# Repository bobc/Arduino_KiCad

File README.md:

# Arduino projects converted to KiCad

This repository contains Eagle projects that have been automatically converted to KiCad (v4) format  by eakit.

The conversion is as far as possible identical to the original, but some features of Eagle cannot be converted directly to KiCad. 

They may (probably will) contain conversion errors - use at own risk!

If you find a conversion problem, please raise an issue here. In case of doubt, the Eagle project should be preferred. 

If you find a problem with the design of a project, or wish to make a feature request,
please do not raise an issue here, contact the original designers.

## Copyright

Copyrights and license terms for each project are as specified by original author(s). 

## Trademarks

Please respect trademarks where applicable, and do not use without permission. 

- "Arduino", "Genuino", and the Arduino logo are trademarks of Arduino AG. https://www.arduino.cc/en/Main/CopyrightNotice

## eakit

eakit project: https://github.com/bobc/eakit

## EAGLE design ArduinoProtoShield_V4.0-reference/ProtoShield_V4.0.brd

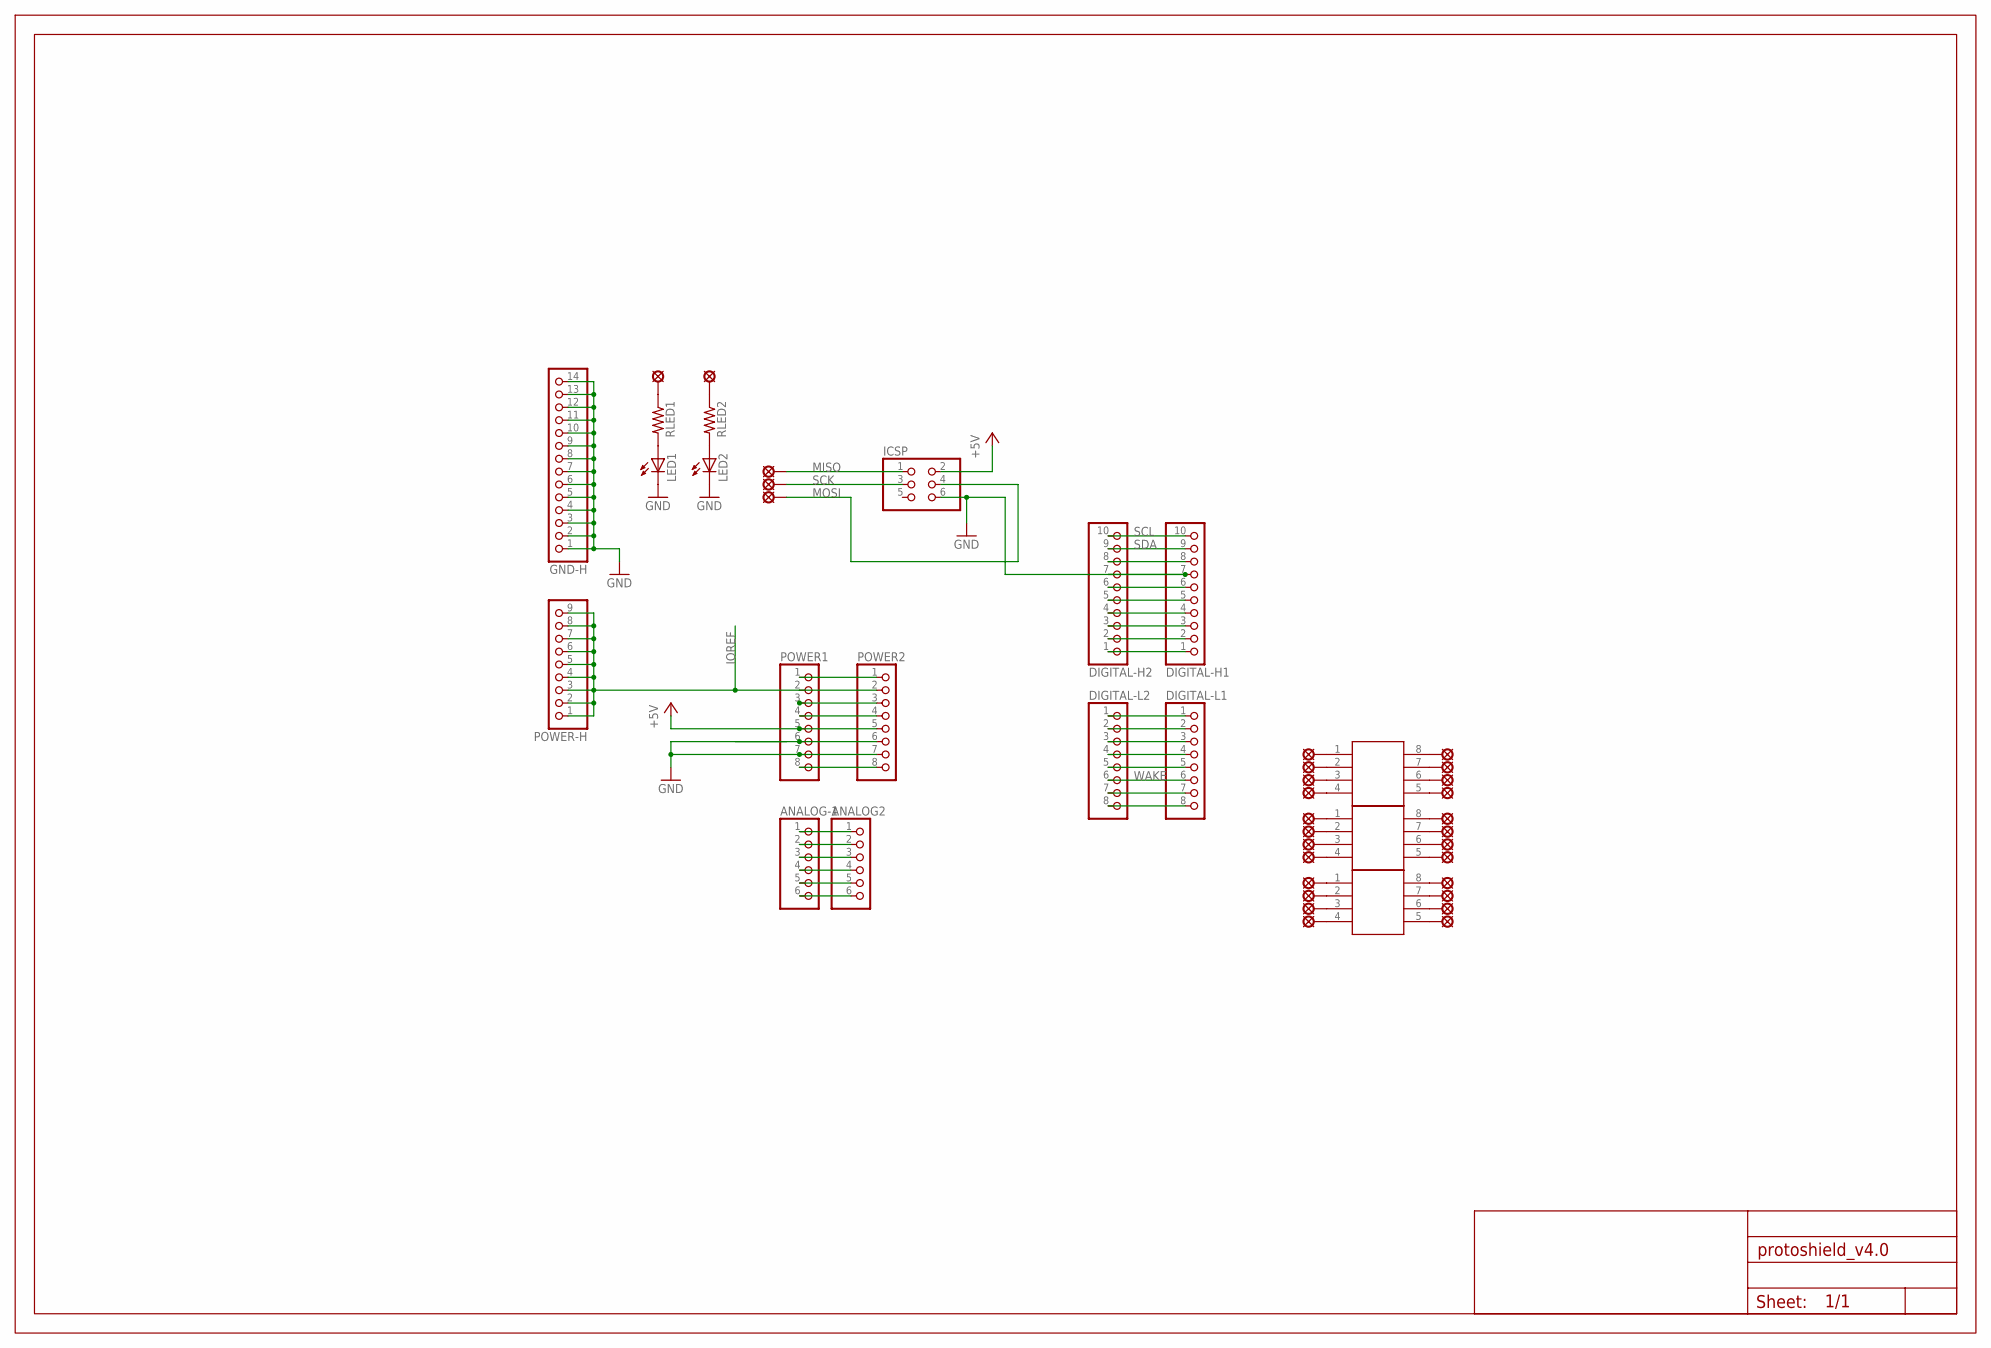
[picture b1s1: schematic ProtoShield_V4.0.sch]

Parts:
ANALOG2: PINHD-1X6; 1X06
ANALOG-1: PINHD-1X6; 1X06
DIGITAL-H1, DIGITAL-H2: PINHD-1X10TH; 1X10-TH
DIGITAL-L1, DIGITAL-L2: PINHD-1X8; 1X08; MPN B67345B0001X087
FRAME1: A3L-LOC; FRAME
GND-H: PINHD-1X14; 1X14; MPN 08051C472KAZ2A
IC1, IC2, IC3: SMD-8; SO-8; MPN MAL215374221E3
ICSP: PINHD-2X3; 2X03; MPN SSF22X035
LED1, LED2: LED3MM; MPN 553-0711F
MISO: LSP10; MPN MDLSP1-04M-01
MOSI: LSP10; MPN MDLSP1-04M-01
P1, P2, P3, P4, P5, P6, P7, P8, P9, P10, P11, P12, P13, P14, P15, P16, P17, P18, P19, P20, P21, P22, P23, P24: LSP10; MPN MDLSP1-04M-01
PLED1, PLED2: LSP10; MPN MDLSP1-04M-01
POWER1, POWER2: PINHD-1X8TH; 1X08-TH
POWER-H: PINHD-1X9; 1X9; MPN 513LF
RLED1, RLED2: 6MM.3; R0207/3
SCK: LSP10; MPN MDLSP1-04M-01

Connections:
+5V: ICSP.2, POWER1.5, POWER2.5
GND: DIGITAL-H1.7, DIGITAL-H2.7, GND-H.1, GND-H.2, GND-H.3, GND-H.4, GND-H.5, GND-H.6, GND-H.7, GND-H.8, GND-H.9, GND-H.10, GND-H.11, GND-H.12, GND-H.13, GND-H.14, ICSP.6, LED1.K (C), LED2.K (C), POWER1.7, POWER2.7
IOREF: POWER1.2, POWER2.2, POWER-H.1, POWER-H.2, POWER-H.3, POWER-H.4, POWER-H.5, POWER-H.6, POWER-H.7, POWER-H.8, POWER-H.9
MISO: ICSP.1, MISO.MP
MOSI: ICSP.4, MOSI.MP
unnamed: DIGITAL-H1.6, DIGITAL-H2.6
unnamed: DIGITAL-H1.1, DIGITAL-H2.1
unnamed: DIGITAL-H1.4, DIGITAL-H2.4
unnamed: DIGITAL-H1.5, DIGITAL-H2.5
unnamed: IC1.1, P1.MP
unnamed: DIGITAL-H1.2, DIGITAL-H2.2
unnamed: DIGITAL-H1.3, DIGITAL-H2.3
unnamed: DIGITAL-L1.1, DIGITAL-L2.1
unnamed: DIGITAL-L1.2, DIGITAL-L2.2
unnamed: DIGITAL-L1.3, DIGITAL-L2.3
unnamed: DIGITAL-L1.4, DIGITAL-L2.4
unnamed: DIGITAL-L1.5, DIGITAL-L2.5
unnamed: DIGITAL-L1.7, DIGITAL-L2.7
unnamed: DIGITAL-L1.8, DIGITAL-L2.8
unnamed: ANALOG2.1, ANALOG-1.1
unnamed: ANALOG2.2, ANALOG-1.2
unnamed: ANALOG2.3, ANALOG-1.3
unnamed: ANALOG2.4, ANALOG-1.4
unnamed: ANALOG2.5, ANALOG-1.5
unnamed: ANALOG2.6, ANALOG-1.6
unnamed: IC1.2, P2.MP
unnamed: POWER1.6, POWER2.6
unnamed: POWER1.3, POWER2.3
unnamed: POWER1.8, POWER2.8
unnamed: POWER1.1, POWER2.1
unnamed: IC1.3, P3.MP
unnamed: IC1.4, P4.MP
unnamed: IC1.8, P24.MP
unnamed: IC1.7, P23.MP
unnamed: IC1.6, P22.MP
unnamed: IC1.5, P21.MP
unnamed: IC2.1, P5.MP
unnamed: IC2.2, P6.MP
unnamed: IC2.3, P7.MP
unnamed: IC2.4, P8.MP
unnamed: IC2.8, P20.MP
unnamed: IC2.7, P19.MP
unnamed: IC2.6, P18.MP
unnamed: IC2.5, P17.MP
unnamed: IC3.1, P9.MP
unnamed: IC3.2, P10.MP
unnamed: IC3.3, P11.MP
unnamed: IC3.4, P12.MP
unnamed: IC3.8, P16.MP
unnamed: IC3.7, P15.MP
unnamed: IC3.6, P14.MP
unnamed: IC3.5, P13.MP
unnamed: LED2.A, RLED2.2
unnamed: LED1.A, RLED1.2
unnamed: PLED1.MP, RLED1.1
unnamed: PLED2.MP, RLED2.1
unnamed: DIGITAL-H1.8, DIGITAL-H2.8
unnamed: POWER1.4, POWER2.4
SCK: ICSP.3, SCK.MP
SCL: DIGITAL-H1.10, DIGITAL-H2.10
SDA: DIGITAL-H1.9, DIGITAL-H2.9
WAKE: DIGITAL-L1.6, DIGITAL-L2.6

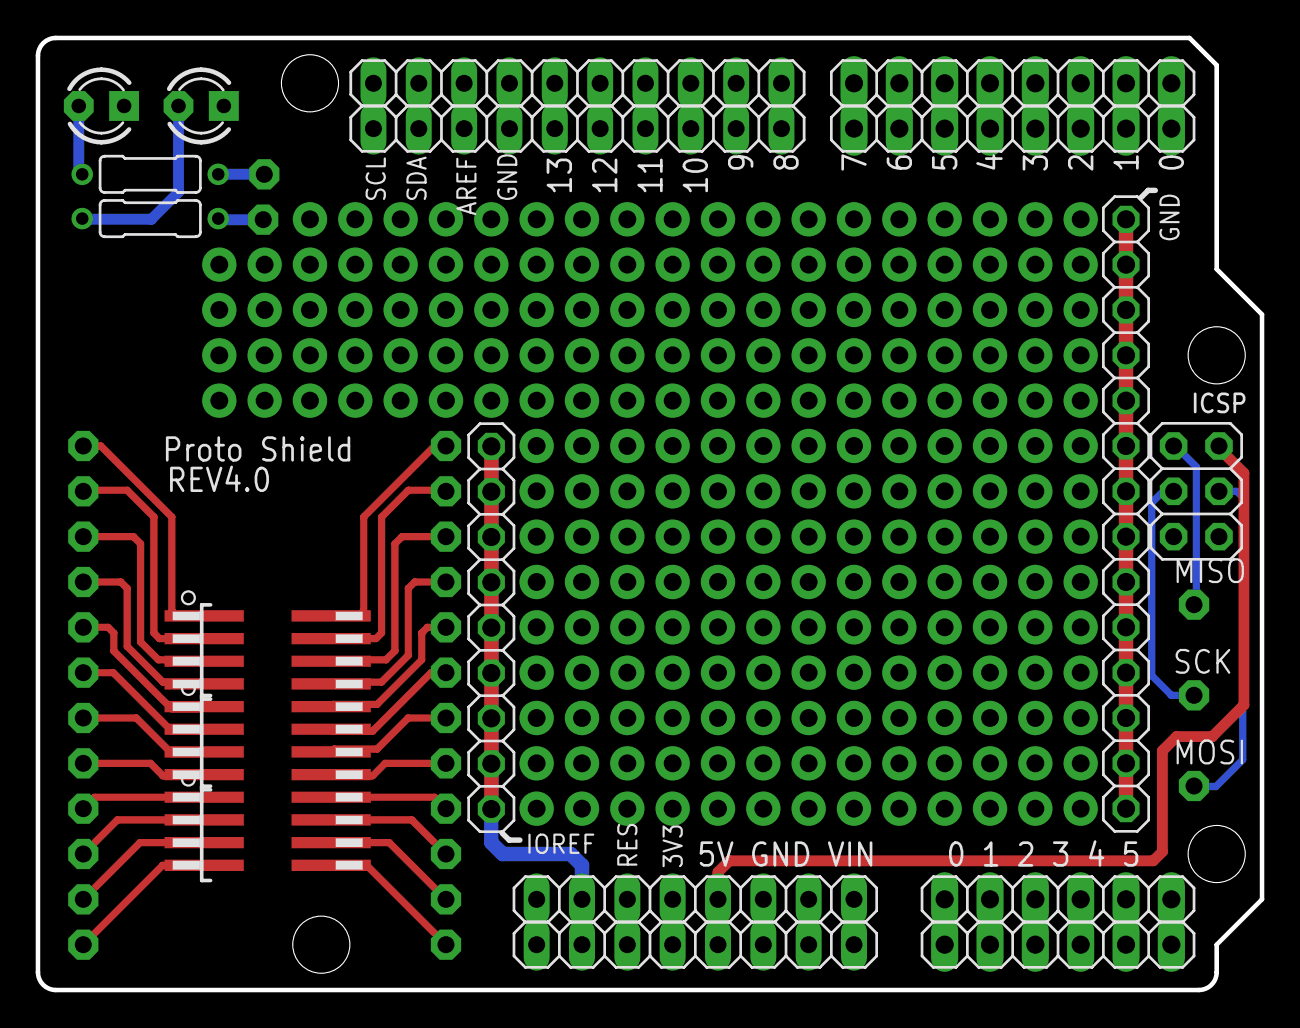
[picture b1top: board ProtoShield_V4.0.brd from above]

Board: 2 copper layers, 68.6 x 53.3 mm, 48 parts (0 on the bottom side), 62 nets.

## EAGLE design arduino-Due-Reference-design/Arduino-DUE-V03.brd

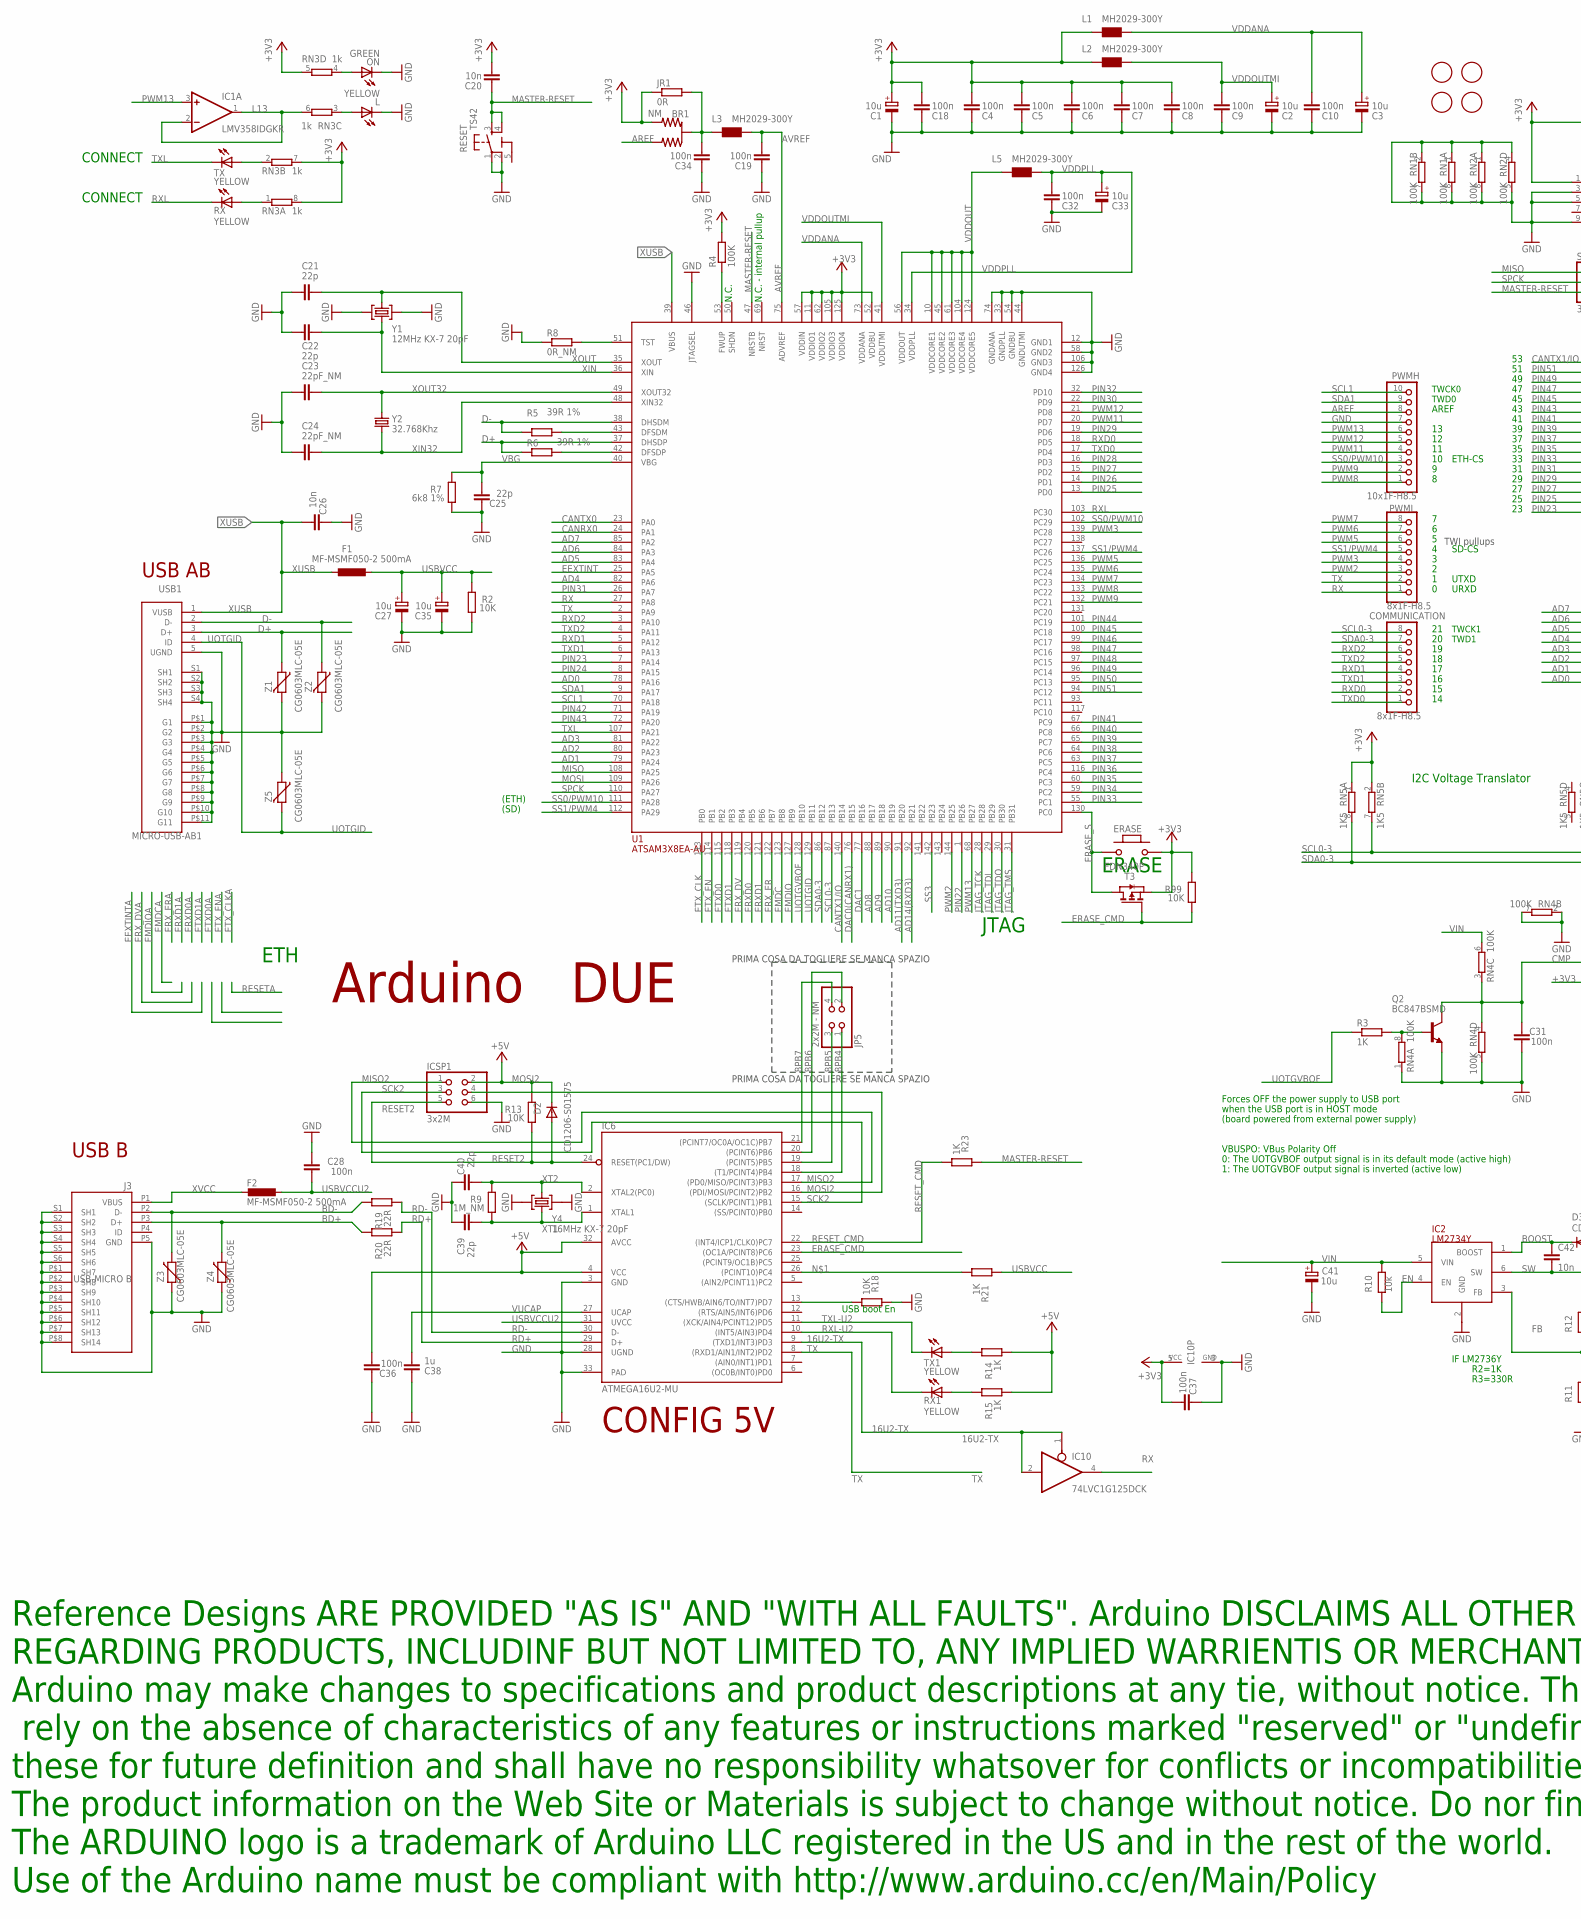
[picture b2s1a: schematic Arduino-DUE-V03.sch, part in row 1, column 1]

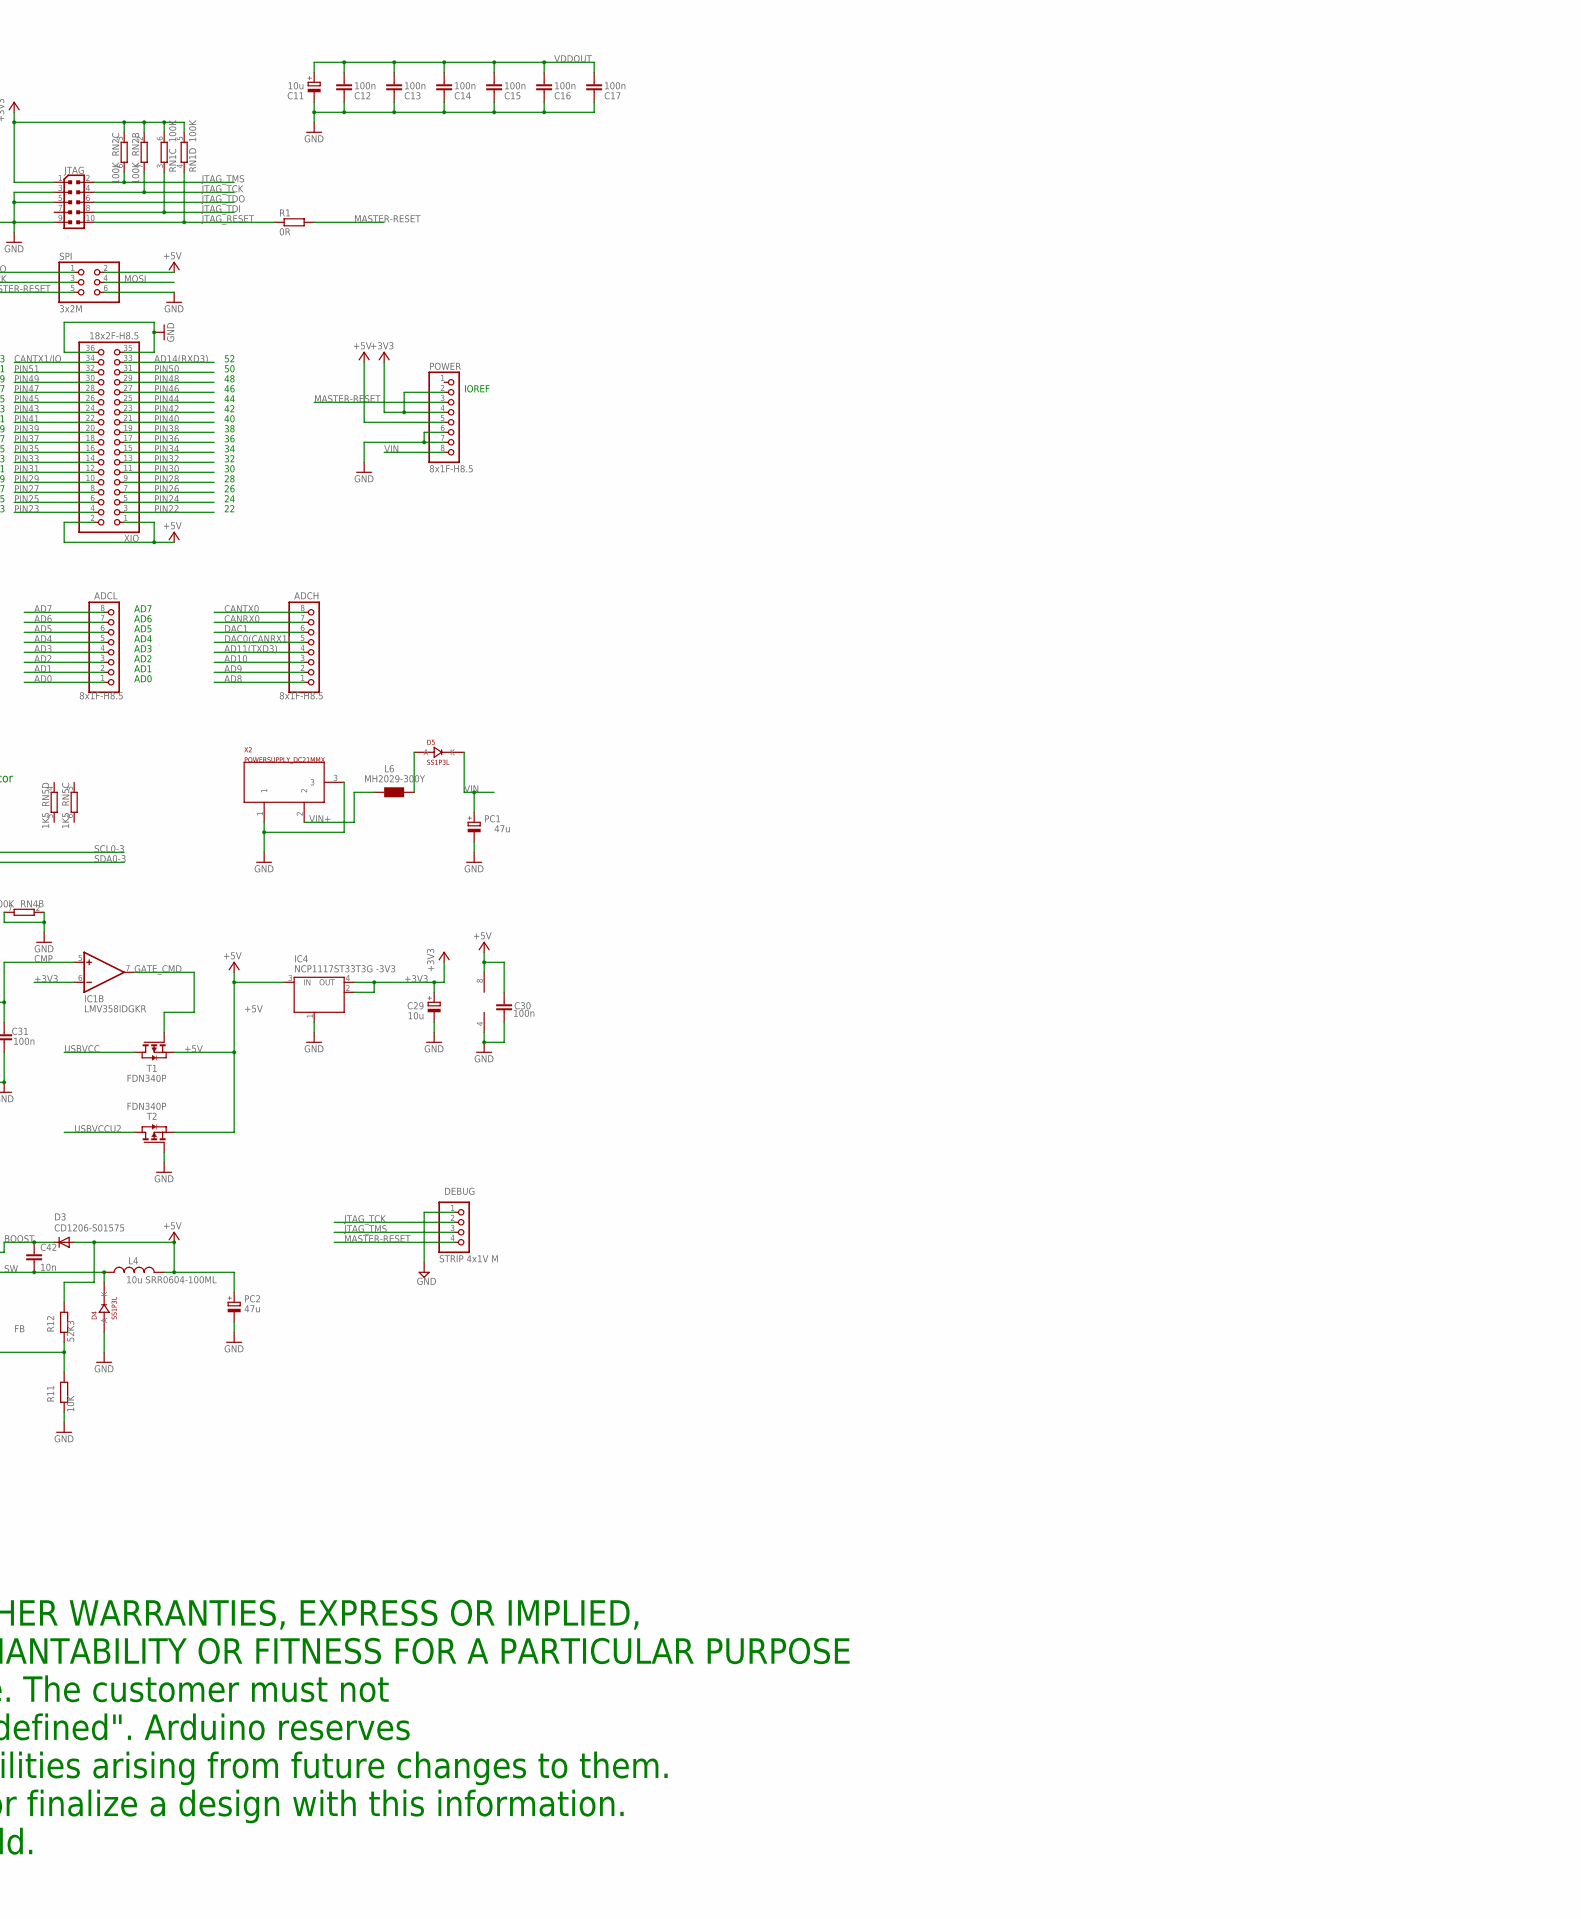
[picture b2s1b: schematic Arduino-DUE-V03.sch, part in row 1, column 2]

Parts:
ADCH: 8x1F-H8.5; 1X08
ADCL: 8x1F-H8.5; 1X08
BR1: NM; J0402
C1, C2, C3, C11, C27, C29, C33, C35, C41: 10u; SMC_B
C4, C5, C6, C7, C8, C9, C10, C12, C13, C14, C15, C16, C17, C18, C19, C28, C30, C31, C32, C34, C36, C37: 100n; C0402
C20, C26: 10n; C0402
C21, C22, C25, C39, C40: 22p; C0402
C23, C24: 22pF_NM; C0402
C38: 1u; C0402
C42: 10n; C0603-ROUND
COMMUNICATION: 8x1F-H8.5; 1X08
D2, D3: CD1206-S01575; MINIMELF
D4, D5: SS1P3L; DO220AAL
DEBUG: STRIP 4x1V M; 1X04
ERASE: MYSMD_PB157; SMD_157SW
F1, F2: MF-MSMF050-2 500mA; L1812
FID1, FID2, FID3, FID4: FIDUCIALMOUNT; FIDUCIA-MOUNT
IC1: LMV358IDGKR; MSOP08
IC2: LM2734Y; SOT23-6
IC4: NCP1117ST33T3G -3V3; SOT223
IC6: ATMEGA16U2-MU; MLF32
IC10: 74LVC1G125DCK; SC70-5
ICSP1: 3x2M; 2X03
J3: USB-MICRO B; CON2_USB_MICRO_B_AT
JP5: 2x2M - NM; 2X02
JR1: 0R; R0402
JTAG: PINHEAD_PINHD-2X5PASSO127; PINHEAD_2X05_127
L: YELLOW; CHIP-LED0805
L1, L2, L3, L5, L6: MH2029-300Y; 0805
L4: 10u SRR0604-100ML; SRR0604
ON: GREEN; CHIP-LED0805
PC1, PC2: 47u; PANASONIC_D
POWER: 8x1F-H8.5; 1X08
PWMH: 10x1F-H8.5; 1X10
PWML: 8x1F-H8.5; 1X08
Q2: BC847BSMD; SOT23
R1: 0R; R0402
R2, R13, R18, R99: 10K; R0402
R3, R14, R15, R21, R23: 1K; R0402
R4: 100K; R0402
R5, R6: 39R 1%; R0402
R7: 6k8 1%; R0603-ROUND
R8: 0R_NM; R0402
R9: 1M_NM; R0402
R10: 10k; R0402
R11: 10K; R0603-ROUND
R12: 52K3; R0603-ROUND
R19, R20: 22R; R0402
RESET: TS42
RN1, RN2, RN4: 100K; CAT16
RN3: 1k; CAY16
RN5: 1K5; CAT16
RX, RX1: YELLOW; CHIP-LED0805
SPI: 3x2M; 2X03
T1, T2, T3: FDN340P; SOT-23
TX, TX1: YELLOW; CHIP-LED0805
U1: ATSAM3X8EA-AU; LQFP144
USB1: MICRO-USB-AB1; MCR-AB1-S-RA-SMT
X2: POWERSUPPLY_DC21MMX; POWERSUPPLY_DC-21MM
XIO: 18x2F-H8.5; 2X18
Y1: 12MHz KX-7 20pF; CRYSTAL-3.2-2.5
Y2: 32.768Khz; RESONATOR_EPSON_FC_145
Y4: 16MHz KX-7 20pF; CRYSTAL-3.2-2.5
Z1, Z2, Z3, Z4, Z5: CG0603MLC-05E; CT/CN0603

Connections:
5-GND: RESET.5 (5-GND)
8PB4: IC6.18 ((T1/PCINT4)PB4), JP5.1
8PB5: IC6.19 ((PCINT5)PB5), JP5.3
8PB6: IC6.20 ((PCINT6)PB6), JP5.2
8PB7: IC6.21 ((PCINT7/OC0A/OC1C)PB7), JP5.4
16U2-TX: IC6.9 ((TXD1/INT3)PD3), IC10.1 (OE), IC10.2 (I)
+3V3: BR1.3 (2), C1.+, C4.2, C5.2, C6.2, C7.2, C8.2, C18.2, C20.2, C29.+, C37.1, ERASE.1, IC1.6 (-IN), IC4.2 (OUT), IC4.4 (OUT), IC10.5 (VCC), JR1.1, JTAG.1, L1.1, L2.1, POWER.2, POWER.4, R4.2, R99.2, RN1.5 (2), RN1.6 (2), RN2.2 (1), RN2.3 (1), RN3.5 (2), RN3.7 (2), RN3.8 (2), RN5.1, RN5.2 (1), T3.2 (S), U1.11 (VDDIO1), U1.52 (VDDBU), U1.57 (VDDIN), U1.62 (VDDIO2), U1.105 (VDDIO3), U1.125 (VDDIO4)
+5V: C30.2, C36.1, D2.C, D3.A, IC1.8 (V+), IC4.3 (IN), IC6.4 (VCC), IC6.32 (AVCC), ICSP1.2, L4.P$2 (2), PC2.+, POWER.5, R12.1, R13.2, R14.1, R15.1, SPI.2, T1.2 (S), T2.2 (S), XIO.1, XIO.2
AD0: ADCL.1, U1.78 (PA16)
AD1: ADCL.2, U1.79 (PA24)
AD2: ADCL.3, U1.80 (PA23)
AD3: ADCL.4, U1.81 (PA22)
AD4: ADCL.5, U1.82 (PA6)
AD5: ADCL.6, U1.83 (PA4)
AD6: ADCL.7, U1.84 (PA3)
AD7: ADCL.8, U1.85 (PA2)
AD8: ADCH.1, U1.88 (PB17)
AD9: ADCH.2, U1.89 (PB18)
AD10: ADCH.3, U1.90 (PB19)
AD11(TXD3): ADCH.4, U1.91 (PB20)
AD14(RXD3): U1.92 (PB21), XIO.33
AREF: BR1.1, PWMH.8
AVREF: C19.2, L3.2, U1.75 (ADVREF)
AVREFL: BR1.2 (C), C34.2, JR1.2, L3.1
BD+: J3.P3 (D+), R20.2, Z4.2
BD-: J3.P2 (D-), R19.2, Z3.2
BOOST: C42.1, D3.C, IC2.1 (BOOST)
CANRX0: ADCH.7, U1.24 (PA1)
CANTX0: ADCH.8, U1.23 (PA0)
CANTX1/IO: U1.140 (PB14), XIO.34
CMP: C31.2, IC1.5 (+IN), Q2.3 (C), RN4.3 (1), RN4.4 (1)
D+: R6.1, U1.37 (DHSDP), USB1.3 (D+), Z1.1
D-: R5.1, U1.38 (DHSDM), USB1.2 (D-), Z2.1
DAC0(CANRX1): ADCH.5, U1.76 (PB15)
DAC1: ADCH.6, U1.77 (PB16)
DTR: IC6.13 ((CTS/HWB/AIN6/TO/INT7)PD7), R18.1
EEXTINT: U1.25 (PA5)
EMDC: U1.123 (PB8)
EMDIO: U1.127 (PB9)
EN: IC2.4 (EN), R10.2
ERASE_CMD: IC6.23 ((OC1A/PCINT8)PC6), R99.1, T3.3 (G)
ERASE_S: ERASE.2, T3.1 (D), U1.130 (PC0)
ERXD0: U1.120 (PB5)
ERXD1: U1.121 (PB6)
ERX_DV: U1.119 (PB4)
ERX_ER: U1.122 (PB7)
ETXD0: U1.115 (PB2)
ETXD1: U1.118 (PB3)
ETX_CLK: U1.113 (PB0)
ETX_EN: U1.114 (PB1)
FB: IC2.3 (FB), R11.1, R12.2
GATE_CMD: IC1.7 (OUT), T1.3 (G)
GND: C1.-, C2.-, C3.-, C4.1, C5.1, C6.1, C7.1, C8.1, C9.1, C10.1, C11.-, C12.1, C13.1, C14.1, C15.1, C16.1, C17.1, C18.1, C19.1, C21.2, C22.2, C23.2, C24.2, C25.2, C26.2, C27.-, C28.2, C29.-, C30.1, C31.1, C32.1, C33.-, C34.1, C35.-, C36.2, C37.2, C38.2, C39.2, C40.2, C41.-, D4.P$2 (A), DEBUG.1, IC1.4 (V-), IC2.2 (GND), IC4.1 (GND/ADJ), IC6.3 (GND), IC6.28 (UGND), IC6.33 (PAD), IC10.3 (GND), ICSP1.6, J3.P5 (GND), J3.P$1 (SH7), J3.P$2 (SH8), J3.P$3 (SH9), J3.P$4 (SH10), J3.P$5 (SH11), J3.P$6 (SH12), J3.P$7 (SH13), J3.P$8 (SH14), J3.S1 (SH1), J3.S2 (SH2), J3.S3 (SH3), J3.S4 (SH4), J3.S5 (SH5), J3.S6 (SH6), JTAG.3, JTAG.5, JTAG.9, L.C, ON.C, PC1.-, PC2.-, POWER.6, POWER.7, PWMH.7, Q2.2 (E), R2.1, R7.1, R8.1, R11.2, R18.2, RESET.1, RESET.2, RN1.1, RN1.2 (1), RN1.7 (2), RN1.8 (2), RN2.1, RN2.4 (1), RN2.5 (2), RN2.8 (2), RN4.1, RN4.2 (1), RN4.5 (2), RN4.7 (2), SPI.6, T2.3 (G), U1.12 (GND1), U1.33 (GNDPLL), U1.44 (GNDUTMI), U1.46 (JTAGSEL), U1.54 (GNDBU), U1.58 (GND2), U1.74 (GNDANA), U1.106 (GND3), U1.126 (GND4), USB1.5 (UGND), USB1.P$1 (G1), USB1.P$2 (G2), USB1.P$3 (G3), USB1.P$4 (G4), USB1.P$5 (G5), USB1.P$6 (G6), USB1.P$7 (G7), USB1.P$8 (G8), USB1.P$9 (G9), USB1.P$10 (G10), USB1.P$11 (G11), USB1.S1 (SH1), USB1.S2 (SH2), USB1.S3 (SH3), USB1.S4 (SH4), X2.1, X2.3, XIO.35, XIO.36, Y1.2 (GND), Y1.4 (GND), Y4.2 (GND), Y4.4 (GND), Z1.2, Z2.2, Z3.1, Z4.1, Z5.1
JTAG_RESET: JTAG.10, R1.1, RN1.4 (1)
JTAG_TCK: DEBUG.2, JTAG.4, RN2.7 (2), U1.28 (PB28)
JTAG_TDI: JTAG.8, RN1.3 (1), U1.29 (PB29)
JTAG_TDO: JTAG.6, U1.30 (PB30)
JTAG_TMS: DEBUG.3, JTAG.2, RN2.6 (2), U1.31 (PB31)
L13: IC1.1 (OUT), IC1.2 (-IN), RN3.6 (2)
MASTER-RESET: C20.1, DEBUG.4, POWER.3, R1.2, R23.2, RESET.3, RESET.4, SPI.5, U1.47 (NRSTB)
MISO: SPI.1, U1.108 (PA25)
MISO2: IC6.17 ((PD0/MISO/PCINT3)PB3), ICSP1.1
MOSI: SPI.4, U1.109 (PA26)
MOSI2: IC6.16 ((PDI/MOSI/PCINT2)PB2), ICSP1.4
unnamed: IC6.26 ((PCINT10)PC4), R21.1
unnamed: L.A, RN3.3 (1)
unnamed: ON.A, RN3.4 (1)
unnamed: R15.2, RX1.A
unnamed: R8.2, U1.51 (TST)
unnamed: Q2.1 (B), R3.2, RN4.8 (2)
unnamed: R4.1, U1.53 (FWUP)
unnamed: D5.P$2 (A), L6.1
unnamed: R5.2, U1.43 (DFSDM)
unnamed: R6.2, U1.42 (DFSDP)
unnamed: R14.2, TX1.A
unnamed: RN3.1, RX.A
unnamed: RN3.2 (1), TX.A
PIN22: U1.1 (PB26), XIO.3
PIN23: U1.7 (PA14), XIO.4
PIN24: U1.8 (PA15), XIO.5
PIN25: U1.13 (PD0), XIO.6
PIN26: U1.14 (PD1), XIO.7
PIN27: U1.15 (PD2), XIO.8
PIN28: U1.16 (PD3), XIO.9
PIN29: U1.19 (PD6), XIO.10
PIN30: U1.22 (PD9), XIO.11
PIN31: U1.26 (PA7), XIO.12
PIN32: U1.32 (PD10), XIO.13
PIN33: U1.55 (PC1), XIO.14
PIN34: U1.59 (PC2), XIO.15
PIN35: U1.60 (PC3), XIO.16
PIN36: U1.116 (PC4), XIO.17
PIN37: U1.63 (PC5), XIO.18
PIN38: U1.64 (PC6), XIO.19
PIN39: U1.65 (PC7), XIO.20
PIN40: U1.66 (PC8), XIO.21
PIN41: U1.67 (PC9), XIO.22
PIN42: U1.71 (PA19), XIO.23
PIN43: U1.72 (PA20), XIO.24
PIN44: U1.101 (PC19), XIO.25
PIN45: U1.100 (PC18), XIO.26
PIN46: U1.99 (PC17), XIO.27
PIN47: U1.98 (PC16), XIO.28
PIN48: U1.97 (PC15), XIO.29
PIN49: U1.96 (PC14), XIO.30
PIN50: U1.95 (PC13), XIO.31
PIN51: U1.94 (PC12), XIO.32
PWM2: PWML.3, U1.144 (PB25)
PWM3: PWML.4, U1.139 (PC28)
PWM5: PWML.6, U1.136 (PC25)
PWM6: PWML.7, U1.135 (PC24)
PWM7: PWML.8, U1.134 (PC23)
PWM8: PWMH.1, U1.133 (PC22)
PWM9: PWMH.2, U1.132 (PC21)
PWM11: PWMH.4, U1.20 (PD7)
PWM12: PWMH.5, U1.21 (PD8)
PWM13: IC1.3 (+IN), PWMH.6, U1.68 (PB27)
RD+: IC6.29 (D+), R20.1
RD-: IC6.30 (D-), R19.1
RESET2: D2.A, IC6.24 (RESET(PC1/DW)), ICSP1.5, R13.1
RESET_CMD: IC6.22 ((INT4/ICP1/CLK0)PC7), R23.1
RX: IC10.4 (O), PWML.1, U1.27 (PA8)
RXD0: COMMUNICATION.2, U1.18 (PD5)
RXD1: COMMUNICATION.4, U1.5 (PA12)
RXD2: COMMUNICATION.6, U1.3 (PA10)
RXL: RX.C, U1.103 (PC30)
RXL-U2: IC6.10 ((INT5/AIN3)PD4), RX1.C
SCK2: IC6.15 ((SCLK/PCINT1)PB1), ICSP1.3
SCL0-3: COMMUNICATION.8, RN5.7 (2), U1.87 (PB13)
SCL1: PWMH.10, U1.70 (PA18)
SDA0-3: COMMUNICATION.7, RN5.8 (2), U1.86 (PB12)
SDA1: PWMH.9, U1.9 (PA17)
SPCK: SPI.3, U1.110 (PA27)
SS0/PWM10: PWMH.3, U1.102 (PC29), U1.111 (PA28)
SS1/PWM4: PWML.5, U1.112 (PA29), U1.137 (PC26)
SS3: U1.142 (PB23)
SW: C42.2, D4.P$1 (K), IC2.6 (SW), L4.P$1 (1)
TX: IC6.8 ((RXD1/AIN1/INT2)PD2), PWML.2, U1.2 (PA9)
TXD0: COMMUNICATION.1, U1.17 (PD4)
TXD1: COMMUNICATION.3, U1.6 (PA13)
TXD2: COMMUNICATION.5, U1.4 (PA11)
TXL: TX.C, U1.107 (PA21)
TXL-U2: IC6.11 ((XCK/AIN4/PCINT12)PD5), TX1.C
UOTGID: U1.129 (PB11), USB1.4 (ID), Z5.2
UOTGVBOF: R3.1, U1.128 (PB10)
USBVCC: C27.+, C35.+, F1.1, R2.2, R21.2, T1.1 (D)
USBVCCU2: C28.1, F2.1, IC6.31 (UVCC), T2.1 (D)
VBG: C25.1, R7.2, U1.40 (VBG)
VDDANA: C3.+, C10.2, L1.2, U1.73 (VDDANA)
VDDOUT: C11.+, C12.2, C13.2, C14.2, C15.2, C16.2, C17.2, L5.1, U1.10 (VDDCORE1), U1.45 (VDDCORE2), U1.56 (VDDOUT), U1.61 (VDDCORE3), U1.104 (VDDCORE4), U1.124 (VDDCORE5)
VDDOUTMI: C2.+, C9.2, L2.2, U1.41 (VDDUTMI)
VDDPLL: C32.2, C33.+, L5.2, U1.34 (VDDPLL)
VIN: C41.+, D5.P$1 (K), IC2.5 (VIN), PC1.+, POWER.8, R10.1, RN4.6 (2)
VIN+: L6.2, X2.2
VUCAP: C38.1, IC6.27 (UCAP)
XIN: C22.1, U1.36 (XIN), Y1.1 (C1)
XIN32: C24.1, U1.48 (XIN32), Y2.P$2 (2)
XOUT: C21.1, U1.35 (XOUT), Y1.3 (C2)
XOUT32: C23.1, U1.49 (XOUT32), Y2.P$1 (1)
XT1: C39.1, IC6.1 (XTAL1), R9.1, Y4.1 (C1)
XT2: C40.1, IC6.2 (XTAL2(PC0)), R9.2, Y4.3 (C2)
XUSB: C26.1, F1.2, U1.39 (VBUS), USB1.1 (VUSB)
XVCC: F2.2, J3.P1 (VBUS)

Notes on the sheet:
TWI pullups
TWCK1
TWD1
IOREF
TWCK0
TWD0
AD1
AD2
AD3
AD4
AD5
AD6
AD0
USB AB
AREF
AD7
SD-CS
Forces OFF the power supply to USB port
when the USB port is in HOST mode
(board powered from external power supply)
N.C.
JTAG
ERASE
CONNECT
VBUSPO: VBus Polarity Off
0: The UOTGVBOF output signal is in its default mode (active high)
1: The UOTGVBOF output signal is inverted (active low)
ETH
UTXD
URXD
(ETH)
(SD)
ETH-CS
I2C Voltage Translator
USB boot En
IF LM2736Y
R2=1K
R3=330R
PRIMA COSA DA TOGLIERE SE MANCA SPAZIO
CONFIG 5V

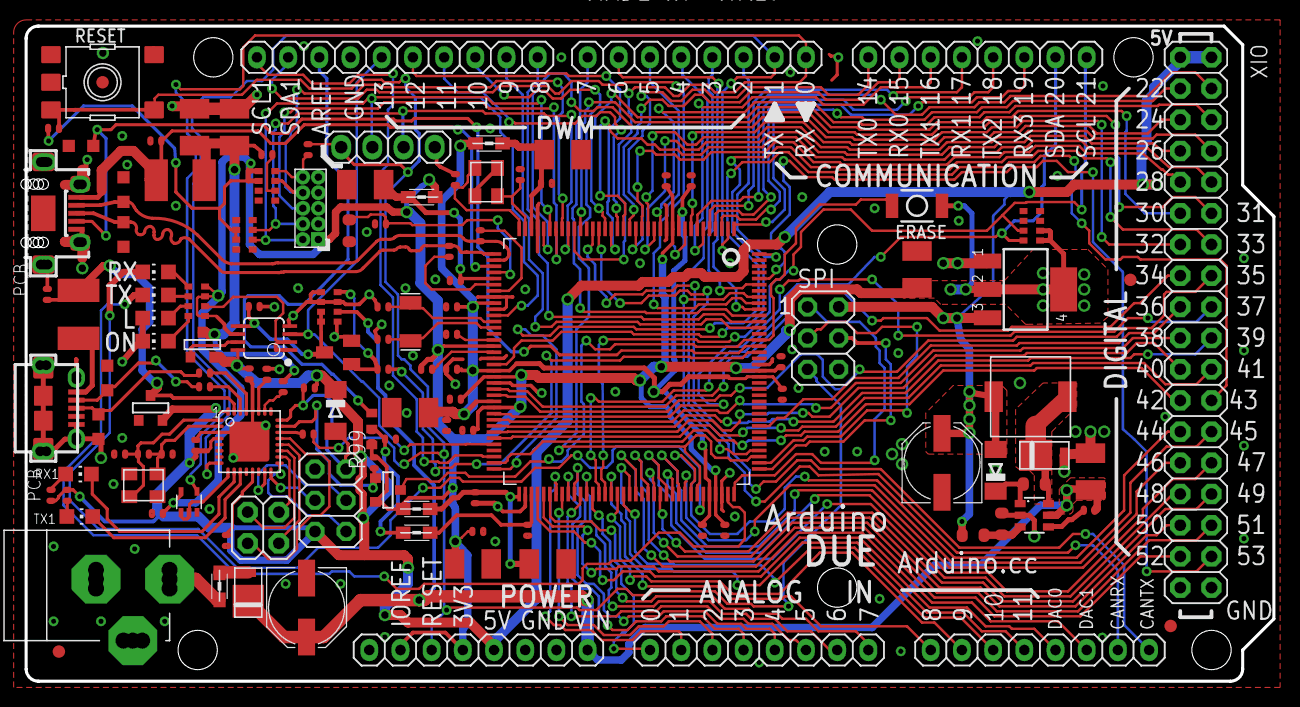
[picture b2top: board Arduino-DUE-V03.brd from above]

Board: 2 copper layers, 101.6 x 53.3 mm, 129 parts (0 on the bottom side), 150 nets.
